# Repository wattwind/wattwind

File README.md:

# WattWind: a fan that knows how hard you're riding

An automatic fan for indoor cycling. A small box with a Raspberry Pi Pico 2 W listens to the heart-rate strap and smart
trainer you already ride with (Bluetooth) and switches your own 3-speed floor fan through relays: off in the warm-up,
full blast in the intervals, and winding down to off when you stop pedaling. Your phone is the remote: the fan serves
its own web page, with no app, no account and no cloud.

**Project site: <https://wattwind.github.io/wattwind/>**: what it does, a [live demo](https://wattwind.github.io/wattwind/demo.html) of the phone page, [all features](https://wattwind.github.io/wattwind/features.html),
the [user manual](https://wattwind.github.io/wattwind/help.html) and the
[build guide](https://wattwind.github.io/wattwind/build.html).

> [!WARNING]
> **This project switches mains voltage (230 V).** Mains can kill. Build it only if you are competent with mains
> wiring, never work on it plugged in, and use an RCD-protected outlet. It is a prototype shared as a hobby project,
> not a certified product: you build and use it at your own risk. Read
> [Safety](https://wattwind.github.io/wattwind/#safety) first.

## What it does

- **Auto:** follows your power (against your FTP), your heart rate (within your own range) or both, up quickly and
  down slowly, one level at a time. Stop pedaling and it winds down by itself.
- **Also an ordinary fan:** Off · 1 · 2 · 3 from the page, an off timer, and it returns to Auto (and off) when forgotten.
- **Several riders, several fans:** up to five rider profiles that switch by whose strap is worn; any number of
  linked fans following one leader over Wi-Fi.
- **Careful by design:** relays off at every start, a hardware watchdog, both mains wires cut when off, an interlock
  that can't power two speeds at once; own Wi-Fi password and PIN at setup, signed firmware updates over Wi-Fi.

## Building one

Everything is in the [build guide](https://wattwind.github.io/wattwind/build.html). In short:

1. Order the PCB (the Gerber ZIP from the [latest release](https://github.com/wattwind/wattwind/releases/latest)) and
   solder 16 through-hole parts (about €70–80 in parts).
2. Copy the project's MicroPython file onto the Pico (from the release: stock MicroPython allows only one Bluetooth
   connection, the fan needs two or three; [why](micropython/README.md)).
3. Copy the `firmware/` folder onto the Pico with Thonny; a relay test clicks through every level.
4. Print the box (print files in the release, or generate them from the Fusion script).
5. Replace the fan's speed switch with a cable to the box.
6. Join the fan's Wi-Fi, choose your own password and PIN, enter your FTP and heart-rate range, ride.

Later firmware updates go over Wi-Fi from the fan's page. To hear about new versions: **Watch → Custom → Releases**
on this page, or **Check for updates** on the fan.

## What's in this repository

| Folder or file | What's in it |
|---|---|
| [`firmware/`](firmware/) | The fan's program (MicroPython) and its web page; [how it works](firmware/README.md) and its tests |
| [`hardware/`](hardware/) | The relay board (KiCad 10) and its [design notes](hardware/DESIGN.md), [parts list](hardware/docs/bom.md) and [prices](hardware/docs/prices.md); the enclosure and cable-entry Fusion scripts |
| [`micropython/`](micropython/) | The patch and build script for the custom MicroPython file, and the licences of what's inside it |
| [`docs/`](docs/) | The project site (GitHub Pages), the user manual and the page demo |
| [`tools/`](tools/) | Release and documentation tools (manifest, signed update file, signing keys, charts, renders) |
| [`CHANGELOG.md`](CHANGELOG.md) | What changed in each release, and whether builders need to do anything |
| [`SECURITY.md`](SECURITY.md) | How to report a security problem |
| [`SECURITY-CHECK.md`](SECURITY-CHECK.md) | The design checked point by point against ETSI EN 303 645 (as a guide, not a certification) |
| [`LICENSE.md`](LICENSE.md) | Which licence covers what |

## Licences

Firmware and tools: MIT. Hardware and mechanical designs: CERN-OHL-P v2. Site, docs and the project's own images:
CC BY 4.0. Third-party code and the custom MicroPython file's drivers keep their own licences. Details:
[LICENSE.md](LICENSE.md).

Provided as is, without warranty of any kind. Designed with AI assistance; built, measured and tested by the author.

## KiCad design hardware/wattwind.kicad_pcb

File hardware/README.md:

# WattWind relay board v3.1

v3.1 (2026-10-30) is v3.0 with a new back silkscreen only (WattWind logo and name, rev 3.1 title
blocks): same copper, parts and holes, so a v3.0 board is electrically the same.

KiCad 10 project for the relay board: 65 × 82 mm, 2 layers, all through-hole. Four Finder 34.51
relays, a Mean Well IRM-02-5, a TBD62003A driver and a Raspberry Pi Pico 2 W (soldered on its pin headers).
Earlier prototypes (v1.0 with Omron relays, v2.0 with 3.5 mm terminals) are not published; `DESIGN.md` says what
changed and why.

## Terminals J1 / J2: any 5.0 or 5.08 mm single-row part

The mains input (J1, 2-pole) and fan output (J2, 4-pole) take any common 5.0 mm or 5.08 mm
PCB terminal block. The pads sit at **5.04 mm**, halfway between the two standards: the outer pin
of a 4-pole part is at most 0.12 mm off, inside the play of the 1.3 mm holes. Oval 1.8 × 3.0 mm
pads leave 3.24 mm between neighbouring mains pads.

| Part (2-pole / 4-pole) | Connection | Notes |
|---|---|---|
| **Phoenix Contact MKDS 1,5/2-5,08 (1715721) / MKDS 1,5/4-5,08 (1715747)** | screw | default in the schematic; hole 1.3 mm; 250 V (III/3) / 400 V (III/2); stocked by all major distributors |
| Phoenix Contact PT 1,5/2-5,0-H (1935161) / PT 1,5/4-5,0-H (1935187) | screw (M2.6, 0.35–0.4 Nm, per the Phoenix catalog) | hole 1.3 mm; pin 1.0 mm |
| WAGO 236-102 / 236-104 | spring (CAGE CLAMP), 45° | "5/5.08 mm"; 1.3 mm hole is loose but solderable |
| WAGO 250-502 / 250-504 | spring (push-in CAGE CLAMP, push-button), 45° | 5.0 mm; 0.75–1.5 mm² stranded wire, no ferrule needed; 320 V (III/3), 17.5 A; pin 0.5 × 0.75 mm is loose in the 1.3 mm hole: hold the part flat while soldering; 16.5 mm tall; body reaches 8.3 mm behind the pin row (DRC-checked: J1 clears H1) |
| Generic 5.0 mm screw terminals (Degson DG301-5.0, "KF301-5.0") | screw | cheapest; check the voltage rating, quality varies |
| Metz Connect, Altech AK300, RND 205-000xx, Würth WR-TBL 5.0/5.08 | screw | check the hole size (1.1–1.4 mm) |

Not compatible: CUI TB007-508 (needs a 1.6 mm hole), parts with two pins per pole or staggered pins.
The wire side faces the board edge (J2: top edge, J1: right edge).

J2 pins left to right on the board: **LOW, MED, HIGH, COM** (pin 1 = COM). J1: **A** (top), **B**.

### Wiring the terminals

Fan and mains cords are usually stranded wire (0.75 mm²). Whichever terminal you choose:

- **Screw terminals: crimp a ferrule on every wire** (0.75 mm², insulated). Bare strands splay
  under the screw and settle over time, and the joint works loose. Never tin the wire ends:
  solder creeps under the clamping pressure and the joint loosens the same way.
- **WAGO 236 (spring clamp):** bare stranded wire is fine. Open the clamp with a screwdriver or
  the WAGO operating tool. Check that the 45° wire entry clears the enclosure lid.
- **WAGO 250-5xx (push-in, push-button):** press the button while inserting bare stranded wire;
  solid wire or ferrules push straight in. Strip 9–10 mm. Check that the 45° wire entry clears
  the enclosure lid.
- Strip only as much as the terminal's datasheet says. No copper should show outside the terminal.
- Give each wire a firm pull test after clamping.
- **Strain relief on the cable at the enclosure wall** (cable gland or clamp). A tug on the cable
  must never reach the terminal. This matters more than which terminal type you pick.

## Before ordering

- The release has the Gerber ZIP ready (`wattwind-v3.1-gerbers.zip`): any PCB maker, default options (2 layers,
  1.6 mm, 1 oz copper). Make your own only after changing the board.
- Check the pin size of the terminals you buy against the 1.3 mm holes, and their 230 VAC rating.
- The enclosure script in `enclosure/` is made for this board and checked in Fusion (no part touches the base or lid).

## Checking the board and making the Gerbers (KiCad 10)

Open `wattwind.kicad_pro` in KiCad 10 to look at or change the board. From the command line (`kicad-cli` comes with
KiCad; on Windows it is in `C:\Program Files\KiCad\10.0\bin\`), run from this folder:

```bash
# ERC: expected 4 findings, all excluded with a comment (see DESIGN.md)
kicad-cli sch erc --severity-all --exit-code-violations -o erc.rpt wattwind.kicad_sch

# DRC: expected 0 violations, 3 commented exclusions. --all-track-errors lists every violation, not one per track
kicad-cli pcb drc --schematic-parity --all-track-errors --refill-zones --severity-all \
    --exit-code-violations -o drc.rpt wattwind.kicad_pcb

# Gerbers (2 layers) and Excellon drill files, then zip production/gerbers/* for the PCB maker
mkdir -p production/gerbers
kicad-cli pcb export gerbers --check-zones --subtract-soldermask \
    -l F.Cu,B.Cu,F.SilkS,B.SilkS,F.Mask,B.Mask,Edge.Cuts -o production/gerbers/ wattwind.kicad_pcb
kicad-cli pcb export drill --format excellon --excellon-units mm --excellon-separate-th \
    --generate-map --map-format gerberx2 -o production/gerbers/ wattwind.kicad_pcb

# The board's 3D model, which the enclosure script loads for its fit check
kicad-cli pcb export step --subst-models --user-origin "172.5x125mm" -o production/wattwind.step wattwind.kicad_pcb

# Parts list
kicad-cli sch export bom -o production/bom.csv wattwind.kicad_sch
```

`production/` is git-ignored except `wattwind.step`. The project footprints for J1 / J2 are made by
`tools/make_terminal_footprints.py` (`WattWind.pretty/`); the relays use KiCad's footprint with a white 3D model
(`3dmodels/`).

More detail: `DESIGN.md` (decisions and why), `docs/bom.md` (parts), `docs/prices.md` (what it costs, where to buy),
`docs/netlist.md` (every pin), `docs/placement.md` (layout).

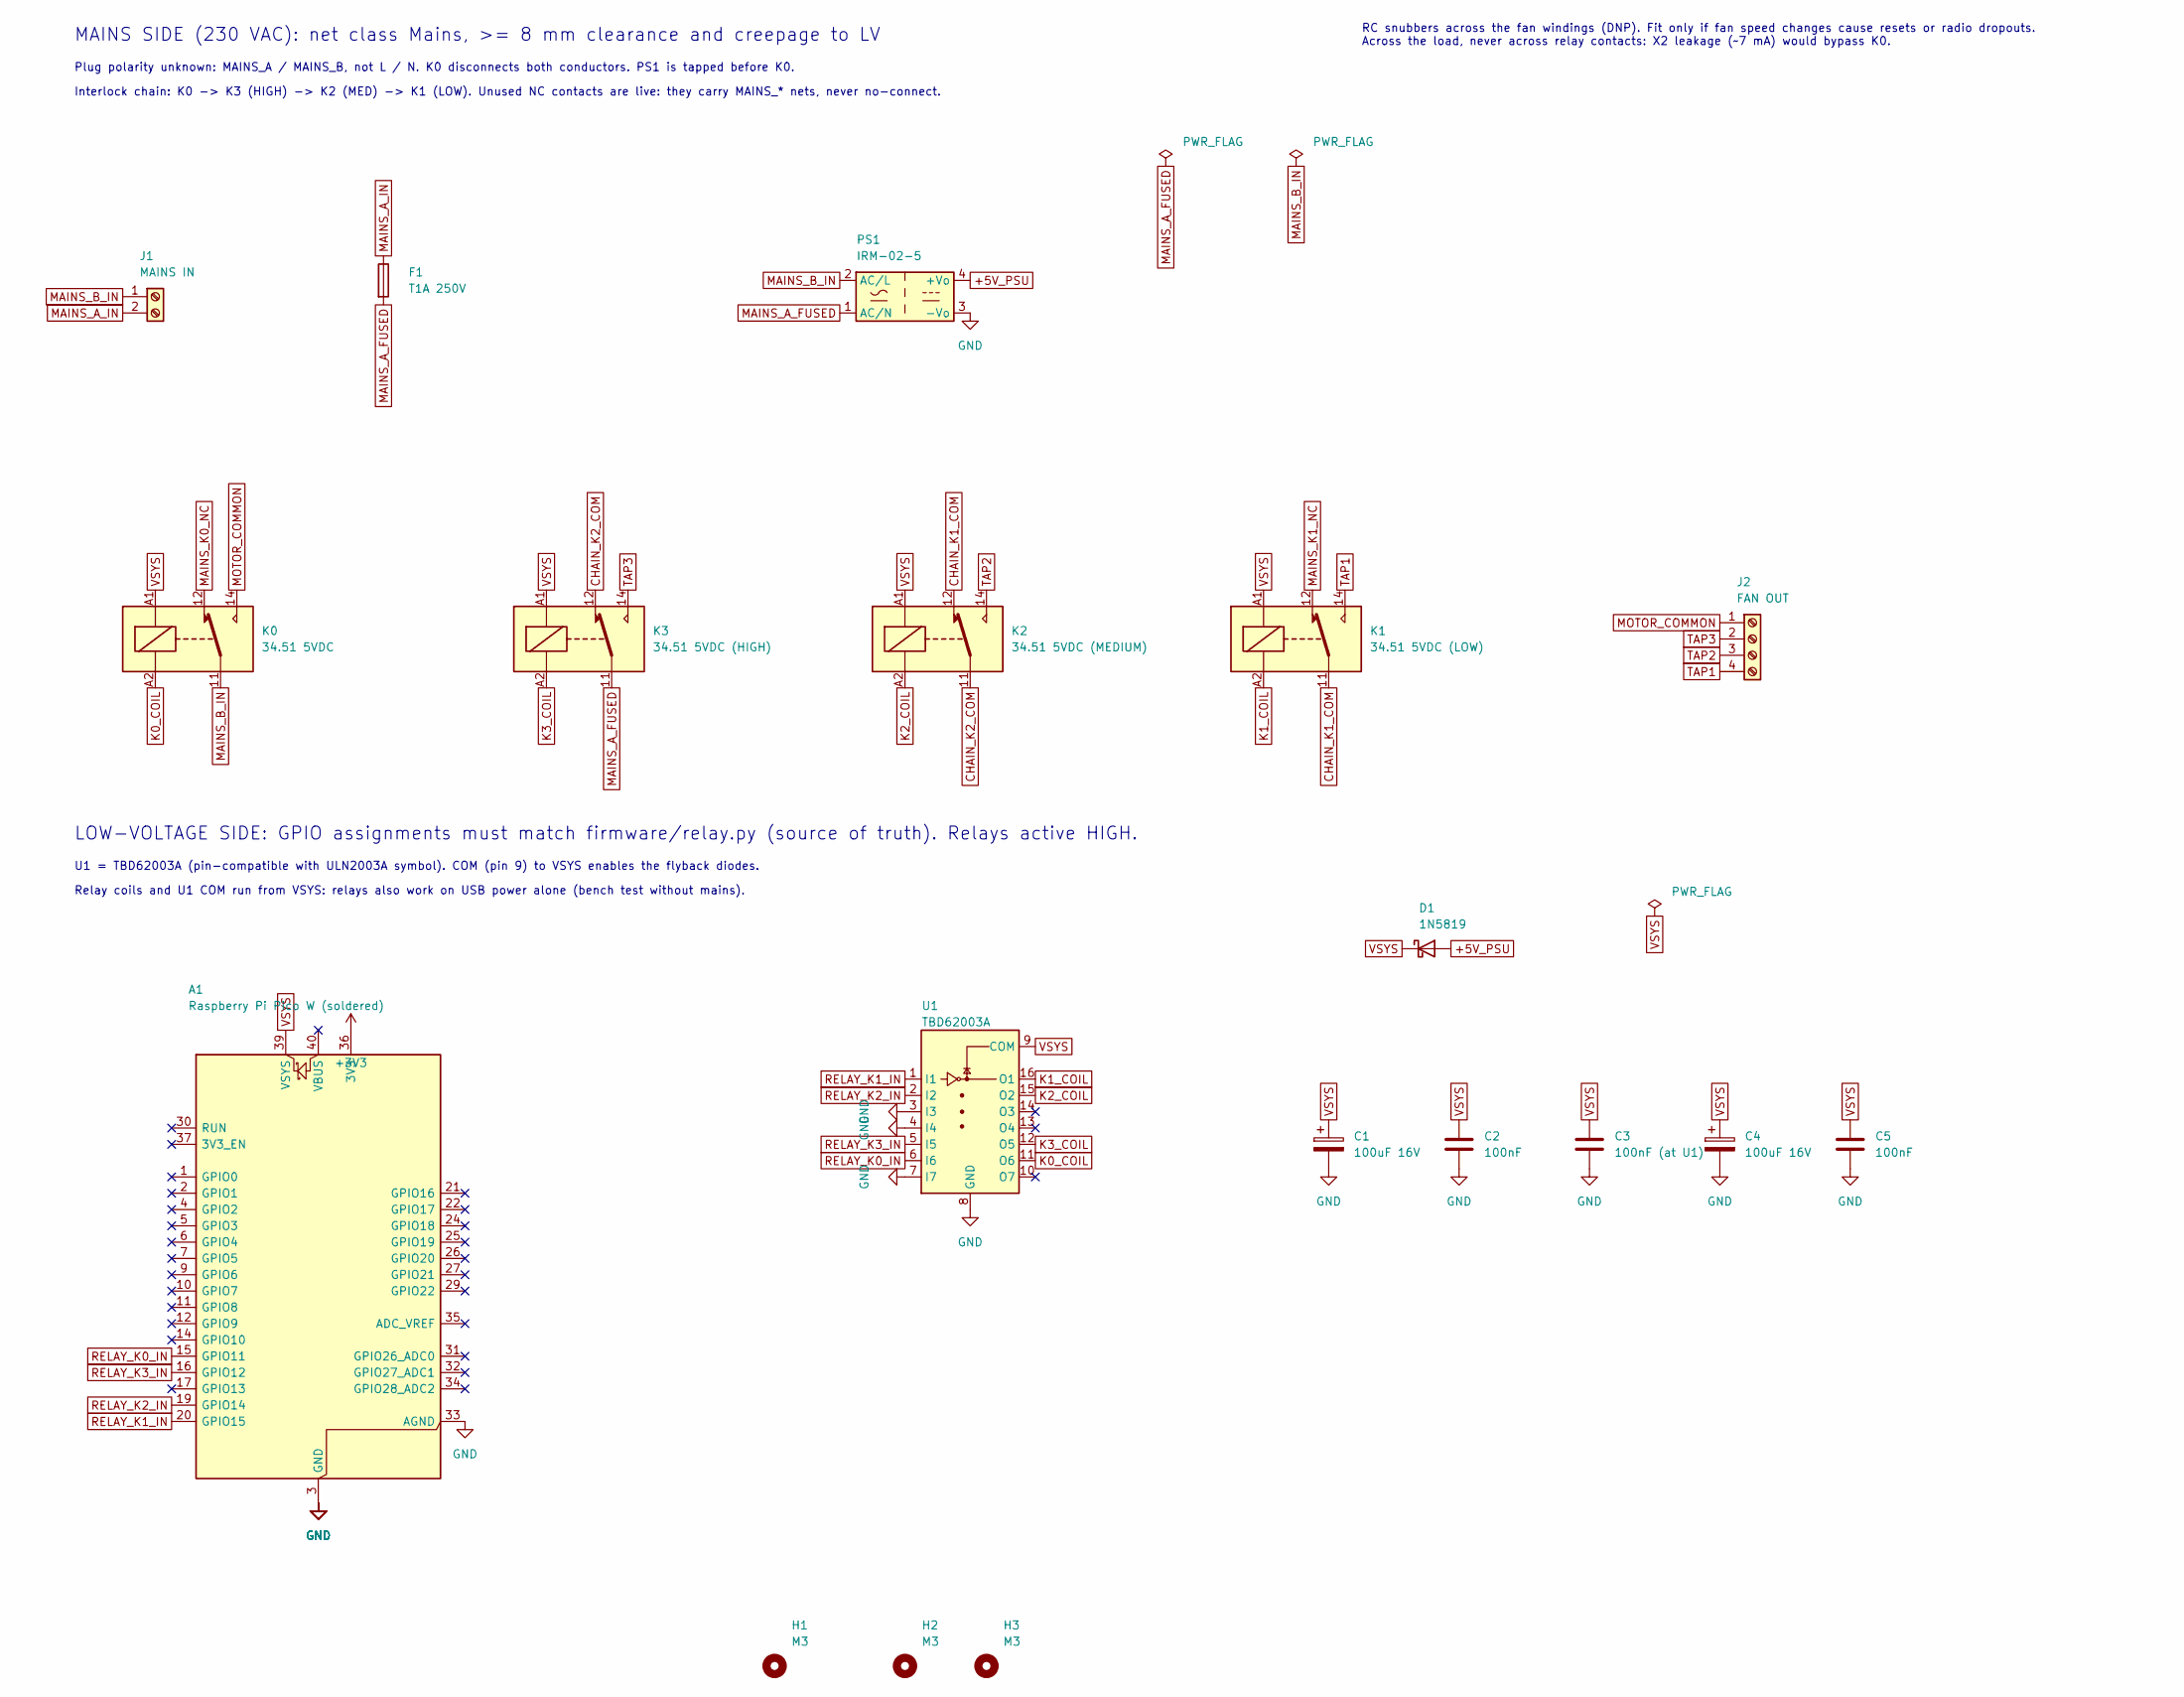
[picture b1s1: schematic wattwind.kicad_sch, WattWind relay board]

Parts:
A1: Raspberry Pi Pico W (soldered); RaspberryPi_Pico_Common_THT; MPN Pico W + 2x 1x20 female header 2.54 mm
C1, C4: 100uF 16V; CP_Radial_D6.3mm_P2.50mm; MPN 100uF 16V electrolytic, D6.3 mm, P2.5 mm
C2, C5: 100nF; C_Disc_D5.0mm_W2.5mm_P5.00mm; MPN 100nF 50V X7R ceramic, 5.0 mm pitch
C3: 100nF (at U1); C_Disc_D5.0mm_W2.5mm_P5.00mm; MPN 100nF 50V X7R ceramic, 5.0 mm pitch
D1: 1N5819; D_DO-41_SOD81_P10.16mm_Horizontal; MPN 1N5819
F1: T1A 250V; Fuseholder_Cylinder-5x20mm_Schurter_0031_8201_Horizontal_Op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; MPN 0031.8201 holder + fuse 5x20 mm T1A 250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
H1, H2, H3: M3; MountingHole_3.2mm_M3
J1: MAINS IN; TerminalBlock_Universal_1x02_P5.04mm_5.0-5.08; MPN MKDS 1,5/2-5,08 (1715721)
J2: FAN OUT; TerminalBlock_Universal_1x04_P5.04mm_5.0-5.08; MPN MKDS 1,5/4-5,08 (1715747)
K0: 34.51 5VDC; Relay_SPDT_Finder_34.51_Vertical; MPN 34.51.7.005.0010
K1: 34.51 5VDC (LOW); Relay_SPDT_Finder_34.51_Vertical; MPN 34.51.7.005.0010
K2: 34.51 5VDC (MEDIUM); Relay_SPDT_Finder_34.51_Vertical; MPN 34.51.7.005.0010
K3: 34.51 5VDC (HIGH); Relay_SPDT_Finder_34.51_Vertical; MPN 34.51.7.005.0010
PS1: IRM-02-5; Converter_ACDC_MeanWell_IRM-02-xx_THT; MPN IRM-02-5
U1: TBD62003A; DIP-16_W7.62mm; MPN TBD62003APG (DIP-16)

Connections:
+3V3: A1.36 (3V3)
+5V_PSU: D1.2 (A), PS1.4 (+Vo)
CHAIN_K1_COM: K1.11, K2.12
CHAIN_K2_COM: K2.11, K3.12
GND: A1.3 (GND), A1.8 (GND), A1.13 (GND), A1.18 (GND), A1.23 (GND), A1.28 (GND), A1.33 (AGND), A1.38 (GND), C1.2, C2.2, C3.2, C4.2, C5.2, PS1.3 (-Vo), U1.3 (I3), U1.4 (I4), U1.7 (I7), U1.8 (GND)
K0_COIL: K0.A2, U1.11 (O6)
K1_COIL: K1.A2, U1.16 (O1)
K2_COIL: K2.A2, U1.15 (O2)
K3_COIL: K3.A2, U1.12 (O5)
MAINS_A_FUSED: F1.2, K3.11, PS1.1 (AC/N)
MAINS_A_IN: F1.1, J1.2
MAINS_B_IN: J1.1, K0.11, PS1.2 (AC/L)
MAINS_K0_NC: K0.12
MAINS_K1_NC: K1.12
MOTOR_COMMON: J2.1, K0.14
RELAY_K0_IN: A1.15 (GPIO11), U1.6 (I6)
RELAY_K1_IN: A1.20 (GPIO15), U1.1 (I1)
RELAY_K2_IN: A1.19 (GPIO14), U1.2 (I2)
RELAY_K3_IN: A1.16 (GPIO12), U1.5 (I5)
TAP1: J2.4, K1.14
TAP2: J2.3, K2.14
TAP3: J2.2, K3.14
VSYS: A1.39 (VSYS), C1.1, C2.1, C3.1, C4.1, C5.1, D1.1 (K), K0.A1, K1.A1, K2.A1, K3.A1, U1.9 (COM)

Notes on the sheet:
Plug polarity unknown: MAINS_A / MAINS_B, not L / N. K0 disconnects both conductors. PS1 is tapped before K0.
RC snubbers across the fan windings (DNP). Fit only if fan speed changes cause resets or radio dropouts. Across the load, never across relay contacts: X2 leakage (~7 mA) would bypass K0.
Interlock chain: K0 -> K3 (HIGH) -> K2 (MED) -> K1 (LOW). Unused NC contacts are live: they carry MAINS_* nets, never no-connect.
LOW-VOLTAGE SIDE: GPIO assignments must match firmware/relay.py (source of truth). Relays active HIGH.
U1 = TBD62003A (pin-compatible with ULN2003A symbol). COM (pin 9) to VSYS enables the flyback diodes.
Relay coils and U1 COM run from VSYS: relays also work on USB power alone (bench test without mains).
MAINS SIDE (230 VAC): net class Mains, >= 8 mm clearance and creepage to LV

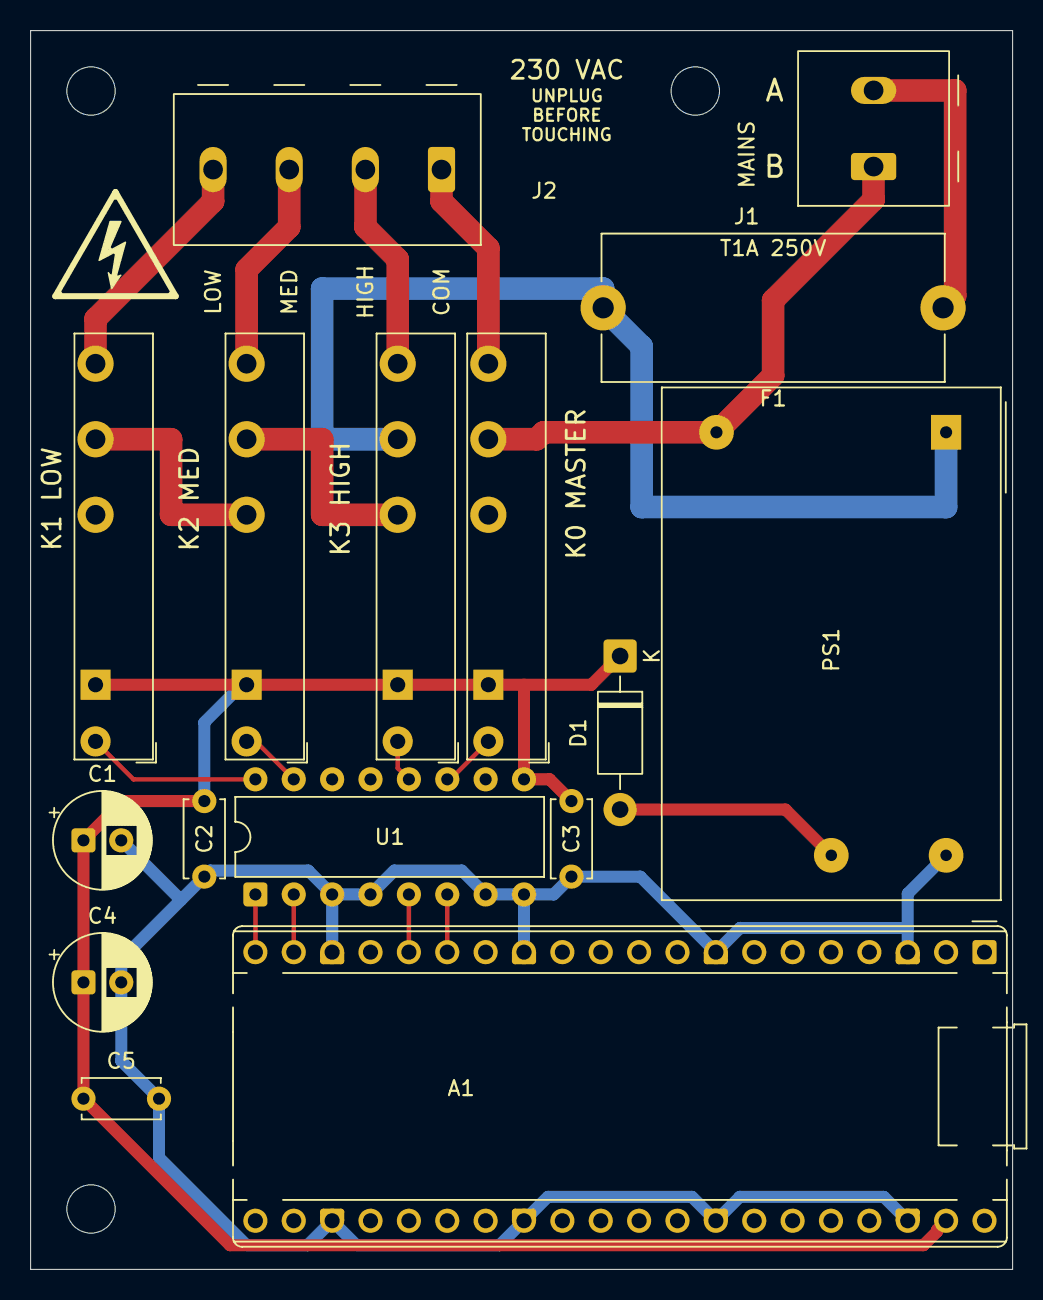
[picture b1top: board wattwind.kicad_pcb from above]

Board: 2 copper layers, 65.0 x 82.0 mm, 21 parts (1 on the bottom side), 20 nets.

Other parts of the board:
G1, G2: Symbol_HighVoltage_Triangle_8x7mm_SilkScreen

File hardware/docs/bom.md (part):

# BOM: WattWind relay board v3.0 / v3.1

v2.0 (2026-10-09) changed K0–K3 to Finder 34.51; v3.0 (2026-10-11) changed J1/J2 to universal
5.0/5.08 mm terminals; v3.1 only changed the back silkscreen. A v3.0 board was built with exactly these parts
(Finder relays, Phoenix MKDS terminals) on 2026-10-24 and has run the author's fan since: every footprint below fits
them. The **VERIFY** notes matter only if you buy a different part than the one named.

Symbol and footprint names were checked against the libraries installed with KiCad 10.0.6.
All VERIFY items below were checked against the real parts on 2026-10-07 (see `../DESIGN.md`): F1 drills changed to 1.4 mm, F1 locating hole removed (RV1 has since been removed).

**VERIFY** means the footprint exists in the library, but you must check it against the
datasheet of the exact part you buy before ordering the PCB.

LCSC part numbers are not filled in. Everything marked "LCSC: to verify" has to be searched
and checked on lcsc.com / JLCPCB parts before ordering.

Assembly: all parts are **through-hole (TH)** and hand-soldered; there are no SMD parts.

## Mains side (TH)

| Ref | Part | Value / rating | KiCad symbol | KiCad footprint | Notes |
|---|---|---|---|---|---|
| J1 | Terminal block, 2-pos, **5.0 or 5.08 mm**, single row | ≥ 250 VAC, ≥ 10 A, 0.75–2.5 mm² wire | `Connector:Screw_Terminal_01x02` | `WattWind:TerminalBlock_Universal_1x02_P5.04mm_5.0-5.08` (project library) | Default part: **Phoenix Contact MKDS 1,5/2-5,08 (1715721)**, screw, hole 1.3 mm, 250 V (III/3) / 400 V (III/2). Also fits: Phoenix PT 1,5/2-5,0-H (1935161; screw, M2.6, pin 1.0 mm, hole 1.3 mm), WAGO 236-102 (spring, 45°, "5/5.08 mm"), WAGO 250-502 (spring push-in with push-button, 45°, 5.0 mm, 0.75–1.5 mm² stranded without ferrule, 320 V III/3, 17.5 A; pin 0.5 × 0.75 mm, loose in 1.3 mm but solderable; body 8.3 mm behind the pin row, clears H1), generic 5.0 mm screw terminals (Degson DG301-5.0, "KF301-5.0"; check the rating), Metz Connect / Altech / RND 5.0–5.08 mm. Pads at 5.04 mm, drill 1.3 mm, oval 1.8 × 3.0 mm: 3.24 mm gap. Wire side towards the right board edge. **VERIFY** the pin size of the part you buy (pins must fit a 1.3 mm hole; CUI TB007 needs 1.6 mm and does not fit). Screw types: ferrules (0.75 mm², insulated) on stranded wire, never tinned ends; spring types take bare stranded wire. Wiring notes in `../README.md`. |
| J2 | Terminal block, 4-pos, **5.0 or 5.08 mm**, single row | as J1 | `Connector:Screw_Terminal_01x04` | `WattWind:TerminalBlock_Universal_1x04_P5.04mm_5.0-5.08` | Default part: **Phoenix Contact MKDS 1,5/4-5,08 (1715747)**. Same alternatives (PT 1,5/4-5,0-H 1935187, WAGO 236-104, WAGO 250-504, generic) and **VERIFY** as J1; outer pins of a 5.0 or 5.08 mm part land 0.12 mm off the pads, inside the hole play. Pin 1 = COM (right), then HIGH, MED, LOW. Wire side towards the top board edge. |
| F1 | Fuse holder 5×20 mm, PCB mount + fuse | 250 VAC; fuse **T1A 250 V**, slow-blow, ceramic body (high breaking capacity, marked "H"), for fans up to ~100 W; **T2A** for fans up to 185 W (relay motor rating, the board's limit) | `Device:Fuse` | `Fuse:Fuseholder_Cylinder-5x20mm_Schurter_0031_8201_Horizontal_Open` | Checked with the part: pin pitch 22.5 mm OK. The real holder has **no locating pin**, so the footprint's 2.7 mm NPTH in the middle is unused (harmless; may be deleted on the board). Legs measured 1.15 mm, too tight for the 1.3 mm drill: set both pad drills to **1.4 mm** on the board (pads stay 3 × 3 mm). Many generic "BLX-A" holders have a different pitch or no locating pin. An open holder should get a snap-on cover. Closed alternative: `Fuse:Fuseholder_Cylinder-5x20mm_Schurter_FAB_0031-355x_Horizontal_Closed`. LCSC: to verify |
| PS1 | Mean Well IRM-02-5 | 5 V 400 mA, 85–264 VAC in, reinforced isolation | `Converter_ACDC:IRM-02-5` | `Converter_ACDC:Converter_ACDC_MeanWell_IRM-02-xx_THT` | **VERIFY** against the Mean Well drawing: AC pins 15.2 mm apart, AC to DC side 28.0 mm, DC pins 7.6 mm apart, pin drills 0.8 / 0.76 mm. LCSC: to verify |
| K0 | Finder **34.51.7.005.0010** | SPDT, 6 A 250 VAC, 5 V DC sensitive coil 170 mW (130 Ω, ~38 mA), AgNi contacts | `Relay:FINDER-34.51` | `WattWind:Relay_SPDT_Finder_34.51_Vertical` (= `Relay_THT` footprint, white 3D model) | Master relay, now **single pole**: switches MAINS_B only (the speed chain switches MAINS_A). Contact pads stay at the library 2.4 mm (2.6 mm gap at 5 mm pitch; allowed by a 2.5 mm DRC exception for relay pads only). **VERIFY** the pin grid against the Finder 34 datasheet: coil pins 3.75 mm apart, contacts 12/11/14 at 11.25 / 16.25 / 21.25 mm from A1, drills 1.0 / 1.3 mm. Must-operate ≈ 0.7 × 5 V = 3.5 V; coil sees about 4.5 V (VSYS minus U1's drop). Plain AgNi contacts (the .5010 gold-flash version only helps for tiny signal loads; at mains the gold burns off). LCSC: to verify |
| K1, K2, K3 | Finder **34.51.7.005.0010** | as K0 | `Relay:FINDER-34.51` | `WattWind:Relay_SPDT_Finder_34.51_Vertical` (= `Relay_THT` footprint, white 3D model) | **Must be SPDT (changeover, 34.51)**: an SPST-NO version has no NC contact, which breaks the interlock chain. Same pad edit and **VERIFY** as K0. LCSC: to verify |

## Low-voltage side

| Ref | Part | Value / rating | KiCad symbol | KiCad footprint | Assy | Notes |
|---|---|---|---|---|---|---|
| A1 | Raspberry Pi **Pico 2 W**, soldered directly on its 2× 1×20 pin headers | | `MCU_Module:RaspberryPi_Pico_W` | `Module:RaspberryPi_Pico_Common_THT` | TH | The symbol's default footprint is the SMD version, so change it. This footprint has 40 TH pads (drill 1.0 mm) and an antenna keep-out. **VERIFY** that the keep-out covers the Pico W antenna area. Buy a Pico 2 WH (headers pre-soldered) or a Pico 2 W plus 2× 1×20 2.54 mm male headers, and solder it onto the board (the older Pico W has the same footprint but is not supported). RP2350 erratum E9: a relay pin left floating can hold a relay on; the firmware never releases them (a later board revision may add 4.7 k pull-downs). Female header sockets also fit (Pico removable), but raise it ~8.5 mm: set the enclosure's user parameter `PicoSocketHeight`. |
| U1 | Toshiba **TBD62003APG**, 7-ch DMOS sink driver, DIP-16 | 50 V, 500 mA/ch, built-in clamp diodes | `Transistor_Array:ULN2003A` (pin-compatible; set the value to TBD62003A) | `Package_DIP:DIP-16_W7.62mm` | TH | Chosen over the ULN2003A for its low output drop (about 0.2 V instead of about 1 V), which keeps about 4.5 V on the coils. The library has no TBD62003A symbol. A DIP-16 socket is optional (the footprint fits one). **VERIFY** in the datasheet that the input "on" threshold is met by 3.3 V GPIO. TME/LCSC: to verify |
| D1 | 1N5819 Schottky | 1 A, 40 V | `Diode:1N5819` | `Diode_THT:D_DO-41_SOD81_P10.16mm_Horizontal` | TH | Cathode band towards VSYS. TME/LCSC: to verify |
| C1, C4 | Electrolytic capacitor | 100 µF, ≥ 16 V | `Device:C_Polarized` | `Capacitor_THT:CP_Radial_D6.3mm_P2.50mm` | TH | **VERIFY** the can diameter and lead pitch. LCSC: to verify |
| C2, C3, C5 | Ceramic capacitor | 100 nF, 50 V, X7R | `Device:C` | `Capacitor_THT:C_Disc_D5.0mm_W2.5mm_P5.00mm` | TH | **VERIFY**: lead pitch 5.0 mm (many MLCCs are 5.08 or 2.54 mm; both 5.0/5.08 fit). TME/LCSC: to verify |
| H1, H2, H3 | Mounting hole M3 | | `Mechanical:MountingHole` | `MountingHole:MountingHole_3.2mm_M3` | — | NPTH. Keep ≥ 6 mm from mains copper (a DRC rule checks this); nylon screw and washer if closer than 7 mm. |

## Off-board

| Part | Notes |
|---|---|
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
